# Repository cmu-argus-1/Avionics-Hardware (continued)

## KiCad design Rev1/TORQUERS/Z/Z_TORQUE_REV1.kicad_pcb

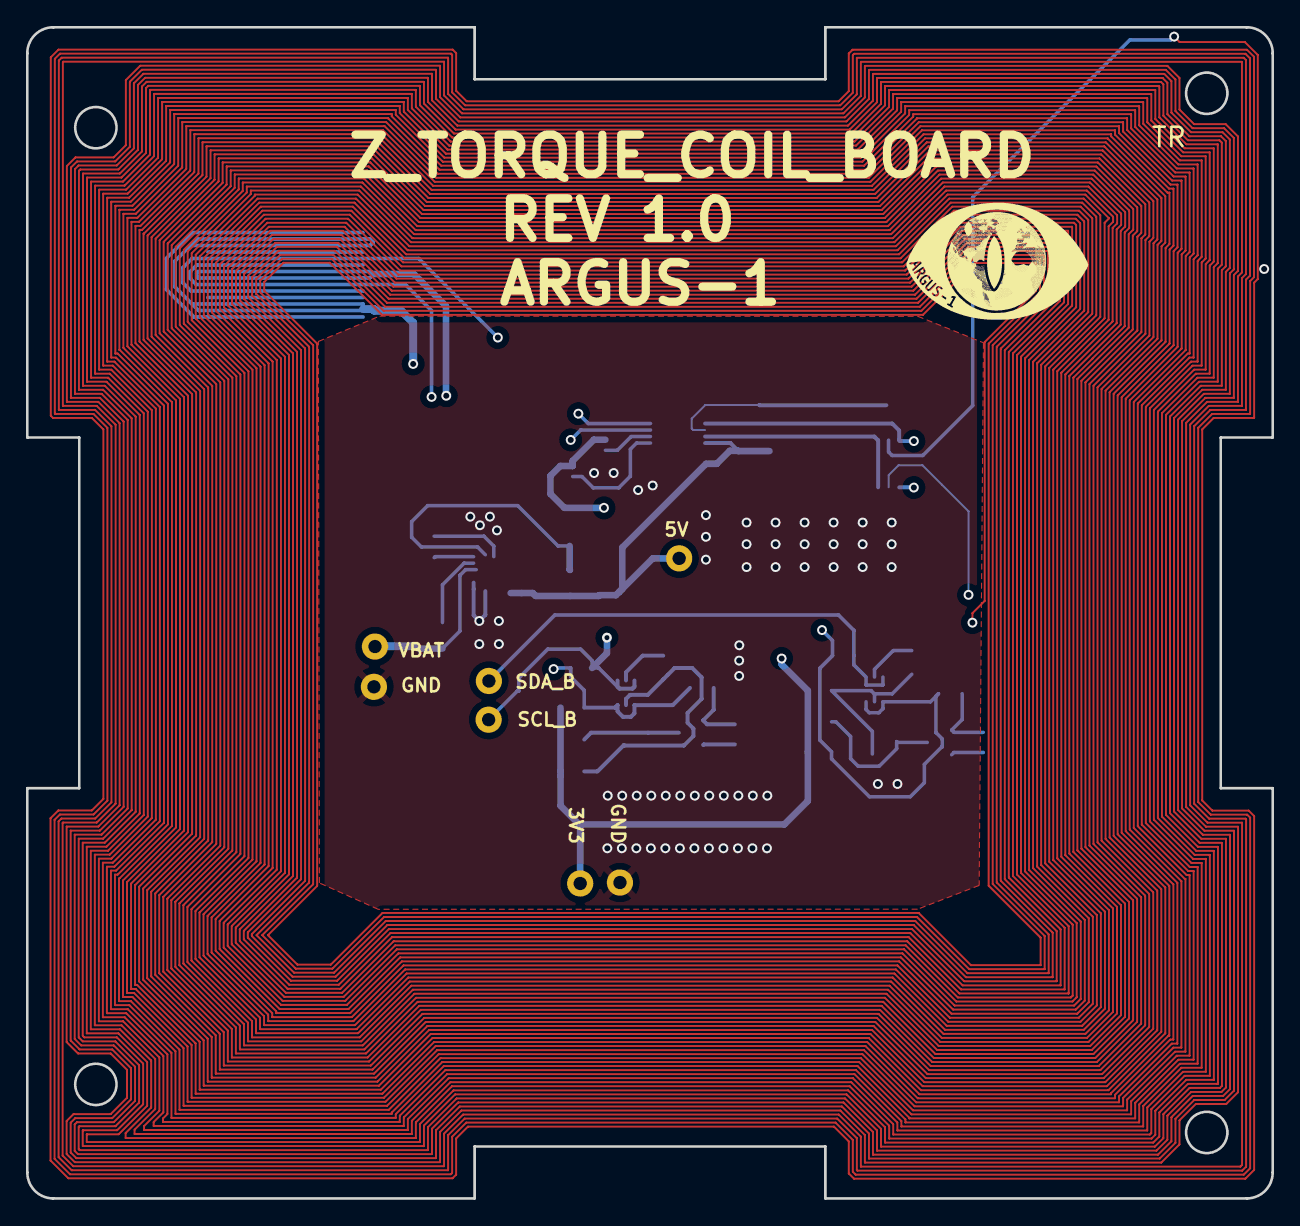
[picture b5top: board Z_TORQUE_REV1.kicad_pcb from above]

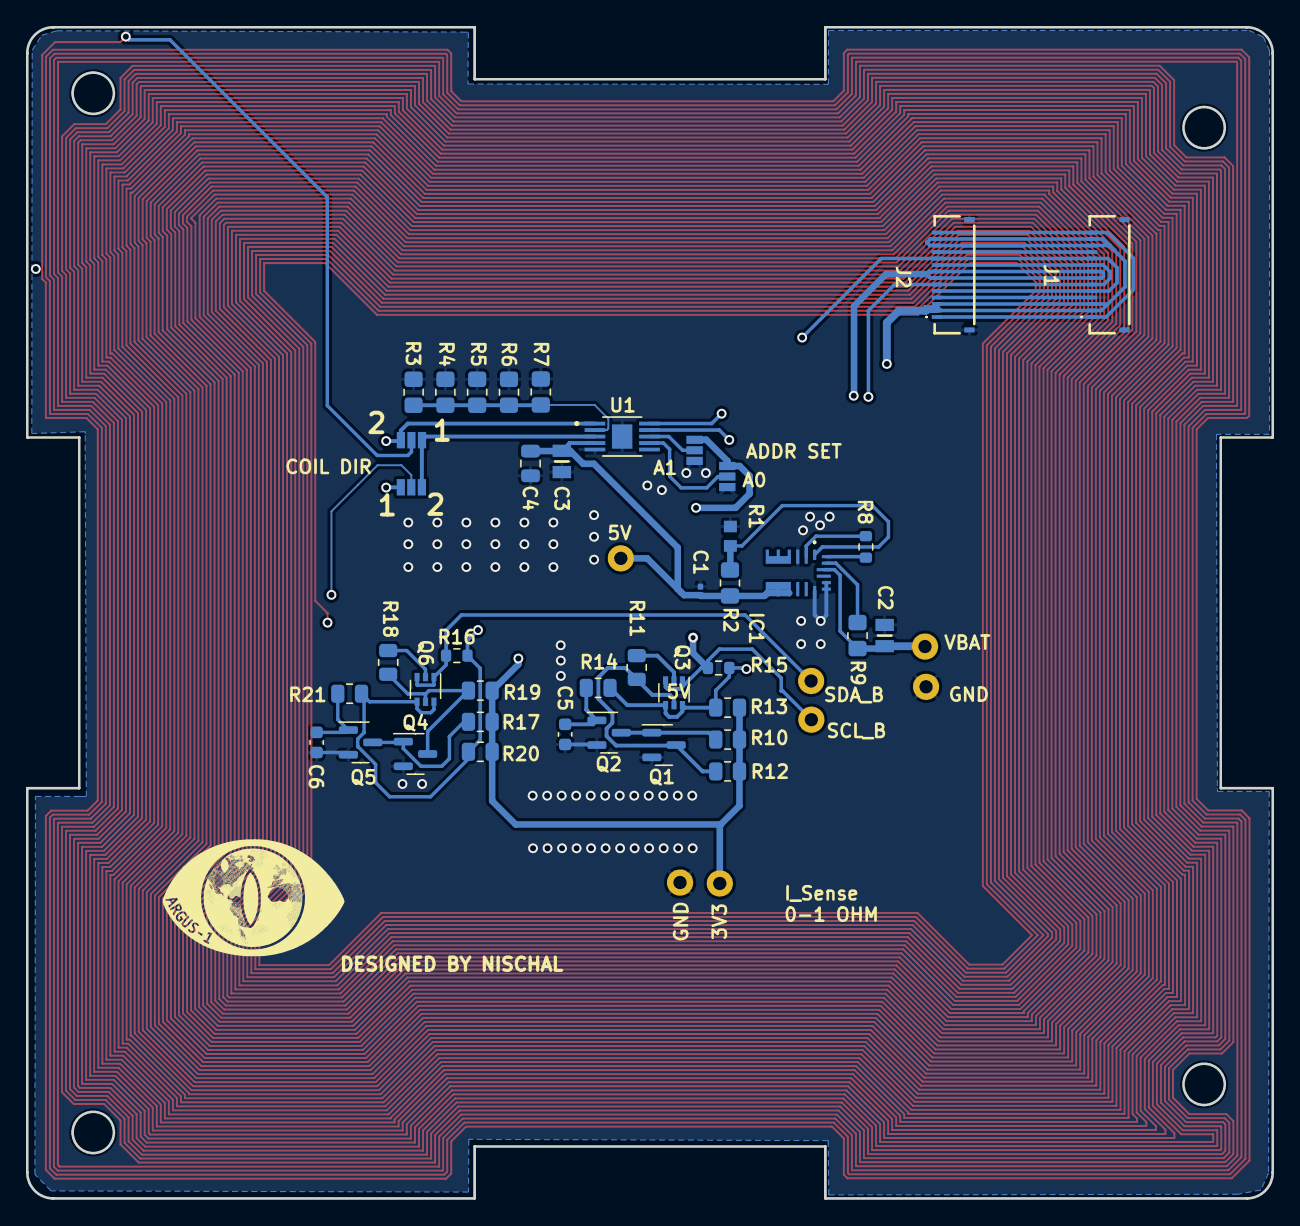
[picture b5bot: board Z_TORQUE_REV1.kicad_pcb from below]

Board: 4 copper layers, 95.9 x 90.2 mm, 43 parts (42 on the bottom side), 28 nets.

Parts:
., .#2: .; Argus LOGO
C1: GRM033R60J224KE15D; CAPC0603X33N
C2, C3: CL21A106KOQNNNE; CAPC2012X140N
C4: 0.1uF; C_0805_2012Metric
C5, C6: 10nF; C_0603_1608Metric
IC1: MPM3610AGQV-Z; MPM3610AGQVZ
J1, J2: F3311A7H121014E200
JP1, JP2, JP3, JP4: SMT-JUMPER_3_NO_NO-SILK
Q1, Q2, Q4, Q5: BSS138; SOT-23
Q3, Q6: MBT2222ADW1T1; SOT-363_SC-70-6
R1: RMCF0603FT19K1; RESC1608X55N
R2, R9: 100K; R_0805_2012Metric_Pad1.20x1.40mm_HandSolder
R3, R4, R5, R6, R7: 0; R_0805_2012Metric_Pad1.20x1.40mm_HandSolder
R8: 100K; R_0603_1608Metric
R10, R12, R13, R17, R19, R20: 10K; R_0805_2012Metric
R11, R18: 600; R_0805_2012Metric
R14, R21: 100K; R_0805_2012Metric
R15, R16: 0; R_0603_1608Metric
U1: DRV8830DGQ; IC_XTR111AIDGQR

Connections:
5V: C1.1, C3.2, C4.1, IC1.7 (OUT_1), IC1.8 (OUT_2), IC1.9 (OUT_3), IC1.22 (OUT_4), R2.1, U1.4 (VCC)
+3.3V: J1.5, J1.10, J2.5, J2.10, JP1.3 (B), JP2.3 (B), R10.2, R12.1, R13.2, R17.2, R19.1, R20.2
/nc: IC1.4 (SW_1), IC1.5 (SW_2), IC1.6 (SW_3), IC1.21 (SW_4)
GND: C1.2, C2.1, C3.1, C4.2, C5.2, C6.2, IC1.3 (AGND), IC1.12 (PGND_1), IC1.13 (PGND_2), IC1.14 (PGND_3), J1.4, J1.11, J1.MP1, J1.MP2, J2.4, J2.11, J2.MP1, J2.MP2, JP1.1 (A), JP2.1 (A), Q1.2 (S), Q2.2 (S), Q4.2 (S), Q5.2 (S), R1.2, R3.2, R4.2, R5.2, R6.2, R7.2, U1.5 (GND), U1.11 (EP)
unnamed: IC1.17 (EN), R9.1
unnamed: IC1.1 (FB), R1.1, R2.2
unnamed: IC1.18 (PG), R8.1
unnamed: IC1.2 (VCC), R8.2
unnamed: JP1.2 (C), U1.8 (A1)
unnamed: JP2.2 (C), U1.7 (A0)
unnamed: JP3.1 (A), JP4.3 (B), U1.1 (OUT2)
unnamed: JP3.3 (B), JP4.1 (A), U1.3 (OUT1)
unnamed: Q1.3 (D), Q3.5 (B2), R11.1, R12.2
unnamed: Q1.1 (G), Q2.3 (D), R10.1
unnamed: C5.1, Q2.1 (G), R14.1
unnamed: Q3.2 (B1), R11.2
unnamed: Q4.3 (D), Q6.5 (B2), R18.2, R19.2
unnamed: Q4.1 (G), Q5.3 (D), R17.1
unnamed: C6.1, Q5.1 (G), R21.1
unnamed: Q6.2 (B1), R18.1
unnamed: R3.1, R4.1, R5.1, R6.1, R7.1, U1.2 (ISENSE)
SCL1_b4iso: J1.6, J1.9, J2.6, J2.9, Q3.1 (E1), Q3.3 (C2), R15.1
SCL_TORQUE: Q3.4 (E2), Q3.6 (C1), R13.1, R14.2, R15.2, U1.10 (SCL)
SDA1_b4iso: J1.7, J1.8, J2.7, J2.8, Q6.1 (E1), Q6.3 (C2), R16.1
SDA_TORQUE: Q6.4 (E2), Q6.6 (C1), R16.2, R20.1, R21.2, U1.9 (SDA)
VBATT: C2.2, IC1.16 (IN), J1.2, J1.3, J1.12, J1.13, J2.2, J2.3, J2.12, J2.13, R9.2
VSOLAR: J1.1, J1.14, J2.1, J2.14
coils: JP3.2 (C), JP4.2 (C)
